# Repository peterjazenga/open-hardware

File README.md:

# open-hardware

This card combines positions for STM32 Bluepill, Arduino Nano and ESP32 Devkit 1 with a breakout area for both SMD and PTH IC's
The power bus is 3v3 from the compute board
It's a quick design for easing rapid prototyping and nothing more
There is no warranty whatsoever with this design, the user assumes all risks and liabilities
Under no circumstances will the author be held liable for use of this design or inability to use this design
No warranty is provided
WARNING: there is no verification of correct layout or function, the user must do their own verification

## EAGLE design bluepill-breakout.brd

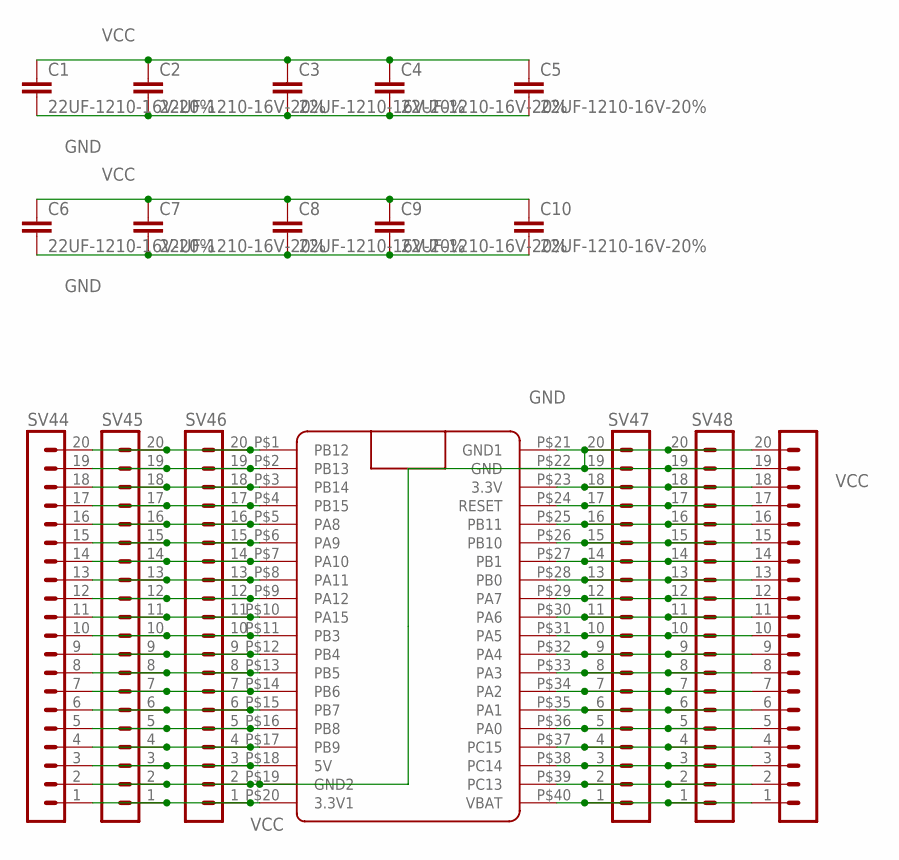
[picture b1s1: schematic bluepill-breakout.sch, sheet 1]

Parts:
C1, C2, C3, C4, C5, C6, C7, C8, C9, C10: 22UF-1210-16V-20%; 1210
SV44, SV45, SV46, SV47, SV48, SV50: MA20-1
U$1: BLUE_PILLADVANCED; BLUE_PILL_ADV

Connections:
GND: C1.2, C2.2, C3.2, C4.2, C5.2, C6.2, C7.2, C8.2, C9.2, C10.2, SV44.2, SV45.2, SV46.2, SV47.19, SV47.20, SV48.19, SV48.20, SV50.19, SV50.20, U$1.P$19 (GND2), U$1.P$21 (GND1), U$1.P$22 (GND); also elsewhere on the board
unnamed: SV44.3, SV45.3, SV46.3, U$1.P$18 (5V)
unnamed: SV44.4, SV45.4, SV46.4, U$1.P$17 (PB9)
unnamed: SV44.5, SV45.5, SV46.5, U$1.P$16 (PB8)
unnamed: SV44.6, SV45.6, SV46.6, U$1.P$15 (PB7)
unnamed: SV44.7, SV45.7, SV46.7, U$1.P$14 (PB6)
unnamed: SV44.8, SV45.8, SV46.8, U$1.P$13 (PB5)
unnamed: SV44.9, SV45.9, SV46.9, U$1.P$12 (PB4)
unnamed: SV44.10, SV45.10, SV46.10, U$1.P$11 (PB3)
unnamed: SV44.11, SV45.11, SV46.11, U$1.P$10 (PA15)
unnamed: SV44.12, SV45.12, SV46.12, U$1.P$9 (PA12)
unnamed: SV44.13, SV45.13, SV46.13, U$1.P$8 (PA11)
unnamed: SV44.14, SV45.14, SV46.14, U$1.P$7 (PA10)
unnamed: SV44.15, SV45.15, SV46.15, U$1.P$6 (PA9)
unnamed: SV44.16, SV45.16, SV46.16, U$1.P$5 (PA8)
unnamed: SV44.17, SV45.17, SV46.17, U$1.P$4 (PB15)
unnamed: SV44.18, SV45.18, SV46.18, U$1.P$3 (PB14)
unnamed: SV44.19, SV45.19, SV46.19, U$1.P$2 (PB13)
unnamed: SV44.20, SV45.20, SV46.20, U$1.P$1 (PB12)
unnamed: SV47.1, SV48.1, SV50.1, U$1.P$40 (VBAT)
unnamed: SV47.2, SV48.2, SV50.2, U$1.P$39 (PC13)
unnamed: SV47.3, SV48.3, SV50.3, U$1.P$38 (PC14)
unnamed: SV47.4, SV48.4, SV50.4, U$1.P$37 (PC15)
unnamed: SV47.5, SV48.5, SV50.5, U$1.P$36 (PA0)
unnamed: SV47.6, SV48.6, SV50.6, U$1.P$35 (PA1)
unnamed: SV47.7, SV48.7, SV50.7, U$1.P$34 (PA2)
unnamed: SV47.8, SV48.8, SV50.8, U$1.P$33 (PA3)
unnamed: SV47.9, SV48.9, SV50.9, U$1.P$32 (PA4)
unnamed: SV47.10, SV48.10, SV50.10, U$1.P$31 (PA5)
unnamed: SV47.11, SV48.11, SV50.11, U$1.P$30 (PA6)
unnamed: SV47.12, SV48.12, SV50.12, U$1.P$29 (PA7)
unnamed: SV47.13, SV48.13, SV50.13, U$1.P$28 (PB0)
unnamed: SV47.14, SV48.14, SV50.14, U$1.P$27 (PB1)
unnamed: SV47.15, SV48.15, SV50.15, U$1.P$26 (PB10)
unnamed: SV47.16, SV48.16, SV50.16, U$1.P$25 (PB11)
unnamed: SV47.17, SV48.17, SV50.17, U$1.P$24 (RESET)
VCC: C1.1, C2.1, C3.1, C4.1, C5.1, C6.1, C7.1, C8.1, C9.1, C10.1, SV44.1, SV45.1, SV46.1, SV47.18, SV48.18, SV50.18, U$1.P$20 (3.3V1), U$1.P$23 (3.3V); also elsewhere on the board

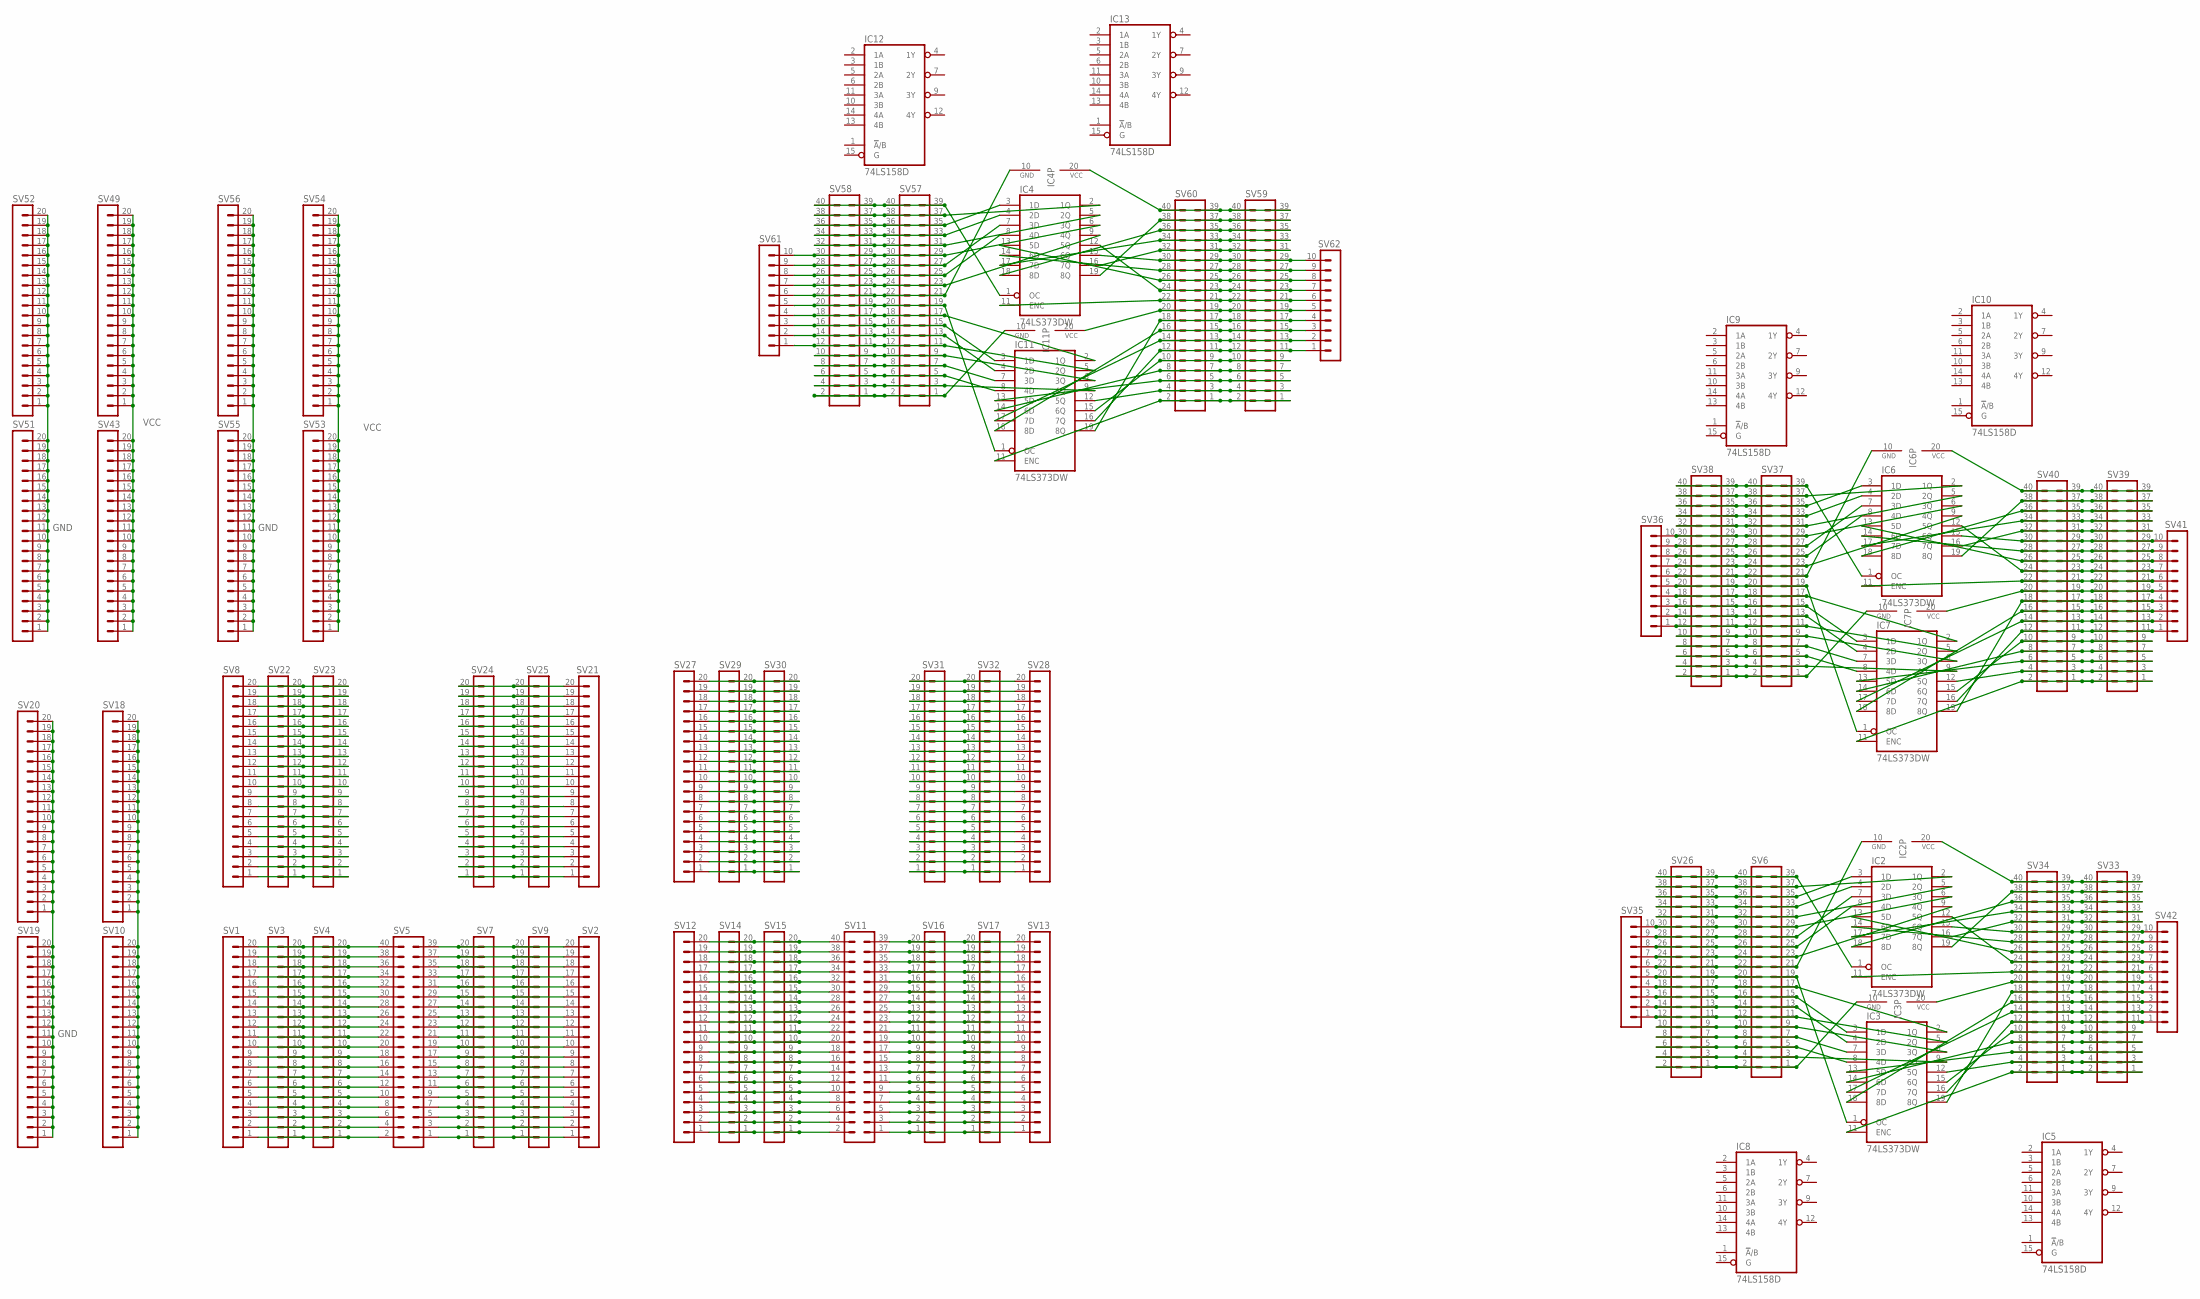
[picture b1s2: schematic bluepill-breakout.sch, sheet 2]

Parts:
IC2, IC3, IC4, IC6, IC7, IC11: 74LS373DW; SO20W
IC5, IC8, IC9, IC10, IC12, IC13: 74LS158D; SO16
SV1, SV2, SV3, SV4, SV7, SV8, SV9, SV10, SV12, SV13, SV14, SV15, SV16, SV17, SV18, SV19, SV20, SV21, SV22, SV23, SV24, SV25, SV27, SV28, SV29, SV30, SV31, SV32, SV43, SV49, SV51, SV52, SV53, SV54, SV55, SV56: MA20-1
SV5, SV6, SV11, SV26, SV33, SV34, SV37, SV38, SV39, SV40, SV57, SV58, SV59, SV60: MA20-2
SV35, SV36, SV41, SV42, SV61, SV62: MA10-1

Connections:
GND: IC5.8 (GND), IC8.8 (GND), IC9.8 (GND), IC10.8 (GND), IC12.8 (GND), IC13.8 (GND), SV19.1, SV19.2, SV19.3, SV19.4, SV19.5, SV19.6, SV19.7, SV19.8, SV19.9, SV19.10, SV19.11, SV19.12, SV19.13, SV19.14, SV19.15, SV19.16, SV19.17, SV19.18, SV19.19, SV19.20, SV20.1, SV20.2, SV20.3, SV20.4, SV20.5, SV20.6, SV20.7, SV20.8, SV20.9, SV20.10, SV20.11, SV20.12, SV20.13, SV20.14, SV20.15, SV20.16, SV20.17, SV20.18, SV20.19, SV20.20, SV51.1, SV51.2, SV51.3, SV51.4, SV51.5, SV51.6, SV51.7, SV51.8, SV51.9, SV51.10, SV51.11, SV51.12, SV51.13, SV51.14, SV51.15, SV51.16, SV51.17, SV51.18, SV51.19, SV51.20, SV52.1, SV52.2, SV52.3, SV52.4, SV52.5, SV52.6, SV52.7, SV52.8, SV52.9, SV52.10, SV52.11, SV52.12, SV52.13, SV52.14, SV52.15, SV52.16, SV52.17, SV52.18, SV52.19, SV52.20, SV55.1, SV55.2, SV55.3, SV55.4, SV55.5, SV55.6, SV55.7, SV55.8, SV55.9, SV55.10, SV55.11, SV55.12, SV55.13, SV55.14, SV55.15, SV55.16, SV55.17, SV55.18, SV55.19, SV55.20, SV56.1, SV56.2, SV56.3, SV56.4, SV56.5, SV56.6, SV56.7, SV56.8, SV56.9, SV56.10, SV56.11, SV56.12, SV56.13, SV56.14, SV56.15, SV56.16, SV56.17, SV56.18, SV56.19, SV56.20; also elsewhere on the board
unnamed: SV1.1, SV3.1, SV4.1, SV5.2
unnamed: SV1.2, SV3.2, SV4.2, SV5.4
unnamed: SV1.3, SV3.3, SV4.3, SV5.6
unnamed: SV1.4, SV3.4, SV4.4, SV5.8
unnamed: SV1.5, SV3.5, SV4.5, SV5.10
unnamed: SV1.6, SV3.6, SV4.6, SV5.12
unnamed: SV1.7, SV3.7, SV4.7, SV5.14
unnamed: SV1.8, SV3.8, SV4.8, SV5.16
unnamed: SV1.9, SV3.9, SV4.9, SV5.18
unnamed: SV1.10, SV3.10, SV4.10, SV5.20
unnamed: SV1.11, SV3.11, SV4.11, SV5.22
unnamed: SV1.12, SV3.12, SV4.12, SV5.24
unnamed: SV1.13, SV3.13, SV4.13, SV5.26
unnamed: SV1.14, SV3.14, SV4.14, SV5.28
unnamed: SV1.15, SV3.15, SV4.15, SV5.30
unnamed: SV1.16, SV3.16, SV4.16, SV5.32
unnamed: SV1.17, SV3.17, SV4.17, SV5.34
unnamed: SV1.18, SV3.18, SV4.18, SV5.36
unnamed: SV1.19, SV3.19, SV4.19, SV5.38
unnamed: SV1.20, SV3.20, SV4.20, SV5.40
unnamed: SV2.1, SV5.1, SV7.1, SV9.1
unnamed: SV2.2, SV5.3, SV7.2, SV9.2
unnamed: SV2.3, SV5.5, SV7.3, SV9.3
unnamed: SV2.4, SV5.7, SV7.4, SV9.4
unnamed: SV2.5, SV5.9, SV7.5, SV9.5
unnamed: SV2.6, SV5.11, SV7.6, SV9.6
unnamed: SV2.7, SV5.13, SV7.7, SV9.7
unnamed: SV2.8, SV5.15, SV7.8, SV9.8
unnamed: SV2.9, SV5.17, SV7.9, SV9.9
unnamed: SV2.10, SV5.19, SV7.10, SV9.10
unnamed: SV2.11, SV5.21, SV7.11, SV9.11
unnamed: SV2.12, SV5.23, SV7.12, SV9.12
unnamed: SV2.13, SV5.25, SV7.13, SV9.13
unnamed: SV2.14, SV5.27, SV7.14, SV9.14
unnamed: SV2.15, SV5.29, SV7.15, SV9.15
unnamed: SV2.16, SV5.31, SV7.16, SV9.16
unnamed: SV2.17, SV5.33, SV7.17, SV9.17
unnamed: SV2.18, SV5.35, SV7.18, SV9.18
unnamed: SV2.19, SV5.37, SV7.19, SV9.19
unnamed: SV2.20, SV5.39, SV7.20, SV9.20
unnamed: SV11.2, SV12.1, SV14.1, SV15.1
unnamed: SV11.4, SV12.2, SV14.2, SV15.2
unnamed: SV11.6, SV12.3, SV14.3, SV15.3
unnamed: SV11.8, SV12.4, SV14.4, SV15.4
unnamed: SV11.10, SV12.5, SV14.5, SV15.5
unnamed: SV11.12, SV12.6, SV14.6, SV15.6
unnamed: SV11.14, SV12.7, SV14.7, SV15.7
unnamed: SV11.16, SV12.8, SV14.8, SV15.8
unnamed: SV11.18, SV12.9, SV14.9, SV15.9
unnamed: SV11.20, SV12.10, SV14.10, SV15.10
unnamed: SV11.22, SV12.11, SV14.11, SV15.11
unnamed: SV11.24, SV12.12, SV14.12, SV15.12
unnamed: SV11.26, SV12.13, SV14.13, SV15.13
unnamed: SV11.28, SV12.14, SV14.14, SV15.14
unnamed: SV11.30, SV12.15, SV14.15, SV15.15
unnamed: SV11.32, SV12.16, SV14.16, SV15.16
unnamed: SV11.34, SV12.17, SV14.17, SV15.17
unnamed: SV11.36, SV12.18, SV14.18, SV15.18
unnamed: SV11.38, SV12.19, SV14.19, SV15.19
unnamed: SV11.40, SV12.20, SV14.20, SV15.20
unnamed: SV11.1, SV13.1, SV16.1, SV17.1
unnamed: SV11.3, SV13.2, SV16.2, SV17.2
unnamed: SV11.5, SV13.3, SV16.3, SV17.3
unnamed: SV11.7, SV13.4, SV16.4, SV17.4
unnamed: SV11.9, SV13.5, SV16.5, SV17.5
unnamed: SV11.11, SV13.6, SV16.6, SV17.6
unnamed: SV11.13, SV13.7, SV16.7, SV17.7
unnamed: SV11.15, SV13.8, SV16.8, SV17.8
unnamed: SV11.17, SV13.9, SV16.9, SV17.9
unnamed: SV11.19, SV13.10, SV16.10, SV17.10
unnamed: SV11.21, SV13.11, SV16.11, SV17.11
unnamed: SV11.23, SV13.12, SV16.12, SV17.12
unnamed: SV11.25, SV13.13, SV16.13, SV17.13
unnamed: SV11.27, SV13.14, SV16.14, SV17.14
unnamed: SV11.29, SV13.15, SV16.15, SV17.15
unnamed: SV11.31, SV13.16, SV16.16, SV17.16
unnamed: SV11.33, SV13.17, SV16.17, SV17.17
unnamed: SV11.35, SV13.18, SV16.18, SV17.18
unnamed: SV11.37, SV13.19, SV16.19, SV17.19
unnamed: SV11.39, SV13.20, SV16.20, SV17.20
unnamed: SV8.1, SV22.1, SV23.1
unnamed: SV8.2, SV22.2, SV23.2
unnamed: SV8.3, SV22.3, SV23.3
unnamed: SV8.4, SV22.4, SV23.4
unnamed: SV8.5, SV22.5, SV23.5
unnamed: SV8.6, SV22.6, SV23.6
unnamed: SV8.7, SV22.7, SV23.7
unnamed: SV8.8, SV22.8, SV23.8
unnamed: SV8.9, SV22.9, SV23.9
unnamed: SV8.10, SV22.10, SV23.10
unnamed: SV8.11, SV22.11, SV23.11
unnamed: SV8.12, SV22.12, SV23.12
unnamed: SV8.13, SV22.13, SV23.13
unnamed: SV8.14, SV22.14, SV23.14
unnamed: SV8.15, SV22.15, SV23.15
unnamed: SV8.16, SV22.16, SV23.16
unnamed: SV8.17, SV22.17, SV23.17
unnamed: SV8.18, SV22.18, SV23.18
unnamed: SV8.19, SV22.19, SV23.19
unnamed: SV8.20, SV22.20, SV23.20
unnamed: SV21.1, SV24.1, SV25.1
unnamed: SV21.2, SV24.2, SV25.2
unnamed: SV21.3, SV24.3, SV25.3
unnamed: SV21.4, SV24.4, SV25.4
unnamed: SV21.5, SV24.5, SV25.5
unnamed: SV21.6, SV24.6, SV25.6
unnamed: SV21.7, SV24.7, SV25.7
unnamed: SV21.8, SV24.8, SV25.8
unnamed: SV21.9, SV24.9, SV25.9
unnamed: SV21.10, SV24.10, SV25.10
unnamed: SV21.11, SV24.11, SV25.11
unnamed: SV21.12, SV24.12, SV25.12
unnamed: SV21.13, SV24.13, SV25.13
unnamed: SV21.14, SV24.14, SV25.14
unnamed: SV21.15, SV24.15, SV25.15
unnamed: SV21.16, SV24.16, SV25.16
unnamed: SV21.17, SV24.17, SV25.17
unnamed: SV21.18, SV24.18, SV25.18
unnamed: SV21.19, SV24.19, SV25.19
unnamed: SV21.20, SV24.20, SV25.20
unnamed: SV27.1, SV29.1, SV30.1
unnamed: SV27.2, SV29.2, SV30.2
unnamed: SV27.3, SV29.3, SV30.3
unnamed: SV27.4, SV29.4, SV30.4
unnamed: SV27.5, SV29.5, SV30.5
unnamed: SV27.6, SV29.6, SV30.6
unnamed: SV27.7, SV29.7, SV30.7
unnamed: SV27.8, SV29.8, SV30.8
unnamed: SV27.9, SV29.9, SV30.9
unnamed: SV27.10, SV29.10, SV30.10
unnamed: SV27.11, SV29.11, SV30.11
unnamed: SV27.12, SV29.12, SV30.12
unnamed: SV27.13, SV29.13, SV30.13
unnamed: SV27.14, SV29.14, SV30.14
unnamed: SV27.15, SV29.15, SV30.15
unnamed: SV27.16, SV29.16, SV30.16
unnamed: SV27.17, SV29.17, SV30.17
unnamed: SV27.18, SV29.18, SV30.18
unnamed: SV27.19, SV29.19, SV30.19
unnamed: SV27.20, SV29.20, SV30.20
unnamed: SV28.1, SV31.1, SV32.1
unnamed: SV28.2, SV31.2, SV32.2
unnamed: SV28.3, SV31.3, SV32.3
unnamed: SV28.4, SV31.4, SV32.4
unnamed: SV28.5, SV31.5, SV32.5
unnamed: SV28.6, SV31.6, SV32.6
unnamed: SV28.7, SV31.7, SV32.7
unnamed: SV28.8, SV31.8, SV32.8
unnamed: SV28.9, SV31.9, SV32.9
unnamed: SV28.10, SV31.10, SV32.10
unnamed: SV28.11, SV31.11, SV32.11
unnamed: SV28.12, SV31.12, SV32.12
unnamed: SV28.13, SV31.13, SV32.13
unnamed: SV28.14, SV31.14, SV32.14
unnamed: SV28.15, SV31.15, SV32.15
unnamed: SV28.16, SV31.16, SV32.16
unnamed: SV28.17, SV31.17, SV32.17
unnamed: SV28.18, SV31.18, SV32.18
unnamed: SV28.19, SV31.19, SV32.19
unnamed: SV28.20, SV31.20, SV32.20
unnamed: IC3.10 (GND), SV6.1, SV6.2, SV26.1, SV26.2
unnamed: IC3.9 (4Q), SV6.3, SV6.4, SV26.3, SV26.4
unnamed: IC3.8 (4D), SV6.5, SV6.6, SV26.5, SV26.6
unnamed: IC3.7 (3D), SV6.7, SV6.8, SV26.7, SV26.8
unnamed: IC3.6 (3Q), SV6.9, SV6.10, SV26.9, SV26.10
unnamed: IC3.5 (2Q), SV6.11, SV6.12, SV26.11, SV26.12, SV35.1
unnamed: IC3.4 (2D), SV6.13, SV6.14, SV26.13, SV26.14, SV35.2
unnamed: IC3.3 (1D), SV6.15, SV6.16, SV26.15, SV26.16, SV35.3
unnamed: IC3.2 (1Q), SV6.17, SV6.18, SV26.17, SV26.18, SV35.4
unnamed: IC3.1 (OC), SV6.19, SV6.20, SV26.19, SV26.20, SV35.5
unnamed: IC2.10 (GND), SV6.21, SV6.22, SV26.21, SV26.22, SV35.6
unnamed: IC2.9 (4Q), SV6.23, SV6.24, SV26.23, SV26.24, SV35.7
unnamed: IC2.8 (4D), SV6.25, SV6.26, SV26.25, SV26.26, SV35.8
unnamed: IC2.7 (3D), SV6.27, SV6.28, SV26.27, SV26.28, SV35.9
unnamed: IC2.6 (3Q), SV6.29, SV6.30, SV26.29, SV26.30, SV35.10
unnamed: IC2.5 (2Q), SV6.31, SV6.32, SV26.31, SV26.32
unnamed: IC2.4 (2D), SV6.33, SV6.34, SV26.33, SV26.34
unnamed: IC2.3 (1D), SV6.35, SV6.36, SV26.35, SV26.36
unnamed: IC2.2 (1Q), SV6.37, SV6.38, SV26.37, SV26.38
unnamed: IC2.1 (OC), SV6.39, SV6.40, SV26.39, SV26.40
unnamed: IC3.11 (ENC), SV33.1, SV33.2, SV34.1, SV34.2
unnamed: IC3.12 (5Q), SV33.3, SV33.4, SV34.3, SV34.4
unnamed: IC3.13 (5D), SV33.5, SV33.6, SV34.5, SV34.6
unnamed: IC3.14 (6D), SV33.7, SV33.8, SV34.7, SV34.8
unnamed: IC3.15 (6Q), SV33.9, SV33.10, SV34.9, SV34.10
unnamed: IC3.16 (7Q), SV33.11, SV33.12, SV34.11, SV34.12, SV42.1
unnamed: IC3.17 (7D), SV33.13, SV33.14, SV34.13, SV34.14, SV42.2
unnamed: IC3.18 (8D), SV33.15, SV33.16, SV34.15, SV34.16, SV42.3
unnamed: IC3.19 (8Q), SV33.17, SV33.18, SV34.17, SV34.18, SV42.4
unnamed: IC3.20 (VCC), SV33.19, SV33.20, SV34.19, SV34.20, SV42.5
unnamed: IC2.11 (ENC), SV33.21, SV33.22, SV34.21, SV34.22, SV42.6
unnamed: IC2.12 (5Q), SV33.23, SV33.24, SV34.23, SV34.24, SV42.7
unnamed: IC2.13 (5D), SV33.25, SV33.26, SV34.25, SV34.26, SV42.8
unnamed: IC2.14 (6D), SV33.27, SV33.28, SV34.27, SV34.28, SV42.9
unnamed: IC2.15 (6Q), SV33.29, SV33.30, SV34.29, SV34.30, SV42.10
unnamed: IC2.16 (7Q), SV33.31, SV33.32, SV34.31, SV34.32
unnamed: IC2.17 (7D), SV33.33, SV33.34, SV34.33, SV34.34
unnamed: IC2.18 (8D), SV33.35, SV33.36, SV34.35, SV34.36
unnamed: IC2.19 (8Q), SV33.37, SV33.38, SV34.37, SV34.38
unnamed: IC2.20 (VCC), SV33.39, SV33.40, SV34.39, SV34.40
unnamed: IC11.9 (4Q), SV57.3, SV57.4, SV58.3, SV58.4
unnamed: IC11.7 (3D), SV57.7, SV57.8, SV58.7, SV58.8
unnamed: IC11.6 (3Q), SV57.9, SV57.10, SV58.9, SV58.10
unnamed: IC11.5 (2Q), SV57.11, SV57.12, SV58.11, SV58.12, SV61.1
unnamed: IC11.3 (1D), SV57.15, SV57.16, SV58.15, SV58.16, SV61.3
unnamed: IC11.2 (1Q), SV57.17, SV57.18, SV58.17, SV58.18, SV61.4
unnamed: IC11.1 (OC), SV57.19, SV57.20, SV58.19, SV58.20, SV61.5
unnamed: IC4.10 (GND), SV57.21, SV57.22, SV58.21, SV58.22, SV61.6
unnamed: IC4.9 (4Q), SV57.23, SV57.24, SV58.23, SV58.24, SV61.7
unnamed: IC4.7 (3D), SV57.27, SV57.28, SV58.27, SV58.28, SV61.9
unnamed: IC4.6 (3Q), SV57.29, SV57.30, SV58.29, SV58.30, SV61.10
unnamed: IC4.5 (2Q), SV57.31, SV57.32, SV58.31, SV58.32
unnamed: IC4.3 (1D), SV57.35, SV57.36, SV58.35, SV58.36
unnamed: IC4.2 (1Q), SV57.37, SV57.38, SV58.37, SV58.38
unnamed: IC4.1 (OC), SV57.39, SV57.40, SV58.39, SV58.40
unnamed: IC11.11 (ENC), SV59.1, SV59.2, SV60.1, SV60.2
unnamed: IC11.12 (5Q), SV59.3, SV59.4, SV60.3, SV60.4
unnamed: IC11.13 (5D), SV59.5, SV59.6, SV60.5, SV60.6
unnamed: IC11.14 (6D), SV59.7, SV59.8, SV60.7, SV60.8
unnamed: IC11.15 (6Q), SV59.9, SV59.10, SV60.9, SV60.10
unnamed: IC11.16 (7Q), SV59.11, SV59.12, SV60.11, SV60.12, SV62.1
unnamed: IC11.17 (7D), SV59.13, SV59.14, SV60.13, SV60.14, SV62.2
unnamed: IC11.18 (8D), SV59.15, SV59.16, SV60.15, SV60.16, SV62.3
unnamed: IC11.19 (8Q), SV59.17, SV59.18, SV60.17, SV60.18, SV62.4
unnamed: IC11.20 (VCC), SV59.19, SV59.20, SV60.19, SV60.20, SV62.5
unnamed: IC4.11 (ENC), SV59.21, SV59.22, SV60.21, SV60.22, SV62.6
unnamed: IC4.12 (5Q), SV59.23, SV59.24, SV60.23, SV60.24, SV62.7
unnamed: IC4.13 (5D), SV59.25, SV59.26, SV60.25, SV60.26, SV62.8
unnamed: IC4.14 (6D), SV59.27, SV59.28, SV60.27, SV60.28, SV62.9
unnamed: IC4.15 (6Q), SV59.29, SV59.30, SV60.29, SV60.30, SV62.10
unnamed: IC4.16 (7Q), SV59.31, SV59.32, SV60.31, SV60.32
unnamed: IC4.17 (7D), SV59.33, SV59.34, SV60.33, SV60.34
unnamed: IC4.18 (8D), SV59.35, SV59.36, SV60.35, SV60.36
unnamed: IC4.19 (8Q), SV59.37, SV59.38, SV60.37, SV60.38
unnamed: IC11.10 (GND), SV57.1, SV57.2, SV58.1, SV58.2
unnamed: IC11.8 (4D), SV57.5, SV57.6, SV58.5, SV58.6
unnamed: IC11.4 (2D), SV57.13, SV57.14, SV58.13, SV58.14, SV61.2
unnamed: IC4.8 (4D), SV57.25, SV57.26, SV58.25, SV58.26, SV61.8
unnamed: IC4.4 (2D), SV57.33, SV57.34, SV58.33, SV58.34
unnamed: IC4.20 (VCC), SV59.39, SV59.40, SV60.39, SV60.40
unnamed: IC7.10 (GND), SV37.1, SV37.2, SV38.1, SV38.2
unnamed: IC7.9 (4Q), SV37.3, SV37.4, SV38.3, SV38.4
unnamed: IC7.8 (4D), SV37.5, SV37.6, SV38.5, SV38.6
unnamed: IC7.7 (3D), SV37.7, SV37.8, SV38.7, SV38.8
unnamed: IC7.6 (3Q), SV37.9, SV37.10, SV38.9, SV38.10
unnamed: IC7.5 (2Q), SV36.1, SV37.11, SV37.12, SV38.11, SV38.12
unnamed: IC7.4 (2D), SV36.2, SV37.13, SV37.14, SV38.13, SV38.14
unnamed: IC7.3 (1D), SV36.3, SV37.15, SV37.16, SV38.15, SV38.16
unnamed: IC7.2 (1Q), SV36.4, SV37.17, SV37.18, SV38.17, SV38.18
unnamed: IC7.1 (OC), SV36.5, SV37.19, SV37.20, SV38.19, SV38.20
unnamed: IC6.10 (GND), SV36.6, SV37.21, SV37.22, SV38.21, SV38.22
unnamed: IC6.9 (4Q), SV36.7, SV37.23, SV37.24, SV38.23, SV38.24
unnamed: IC6.8 (4D), SV36.8, SV37.25, SV37.26, SV38.25, SV38.26
unnamed: IC6.7 (3D), SV36.9, SV37.27, SV37.28, SV38.27, SV38.28
unnamed: IC6.6 (3Q), SV36.10, SV37.29, SV37.30, SV38.29, SV38.30
unnamed: IC6.5 (2Q), SV37.31, SV37.32, SV38.31, SV38.32
unnamed: IC6.4 (2D), SV37.33, SV37.34, SV38.33, SV38.34
unnamed: IC6.3 (1D), SV37.35, SV37.36, SV38.35, SV38.36
unnamed: IC6.2 (1Q), SV37.37, SV37.38, SV38.37, SV38.38
unnamed: IC6.1 (OC), SV37.39, SV37.40, SV38.39, SV38.40
unnamed: IC7.11 (ENC), SV39.1, SV39.2, SV40.1, SV40.2
unnamed: IC7.12 (5Q), SV39.3, SV39.4, SV40.3, SV40.4
unnamed: IC7.13 (5D), SV39.5, SV39.6, SV40.5, SV40.6
unnamed: IC7.14 (6D), SV39.7, SV39.8, SV40.7, SV40.8
unnamed: IC7.15 (6Q), SV39.9, SV39.10, SV40.9, SV40.10
unnamed: IC7.16 (7Q), SV39.11, SV39.12, SV40.11, SV40.12, SV41.1
unnamed: IC7.17 (7D), SV39.13, SV39.14, SV40.13, SV40.14, SV41.2
unnamed: IC7.18 (8D), SV39.15, SV39.16, SV40.15, SV40.16, SV41.3
unnamed: IC7.19 (8Q), SV39.17, SV39.18, SV40.17, SV40.18, SV41.4
unnamed: IC7.20 (VCC), SV39.19, SV39.20, SV40.19, SV40.20, SV41.5
unnamed: IC6.11 (ENC), SV39.21, SV39.22, SV40.21, SV40.22, SV41.6
unnamed: IC6.12 (5Q), SV39.23, SV39.24, SV40.23, SV40.24, SV41.7
unnamed: IC6.13 (5D), SV39.25, SV39.26, SV40.25, SV40.26, SV41.8
unnamed: IC6.14 (6D), SV39.27, SV39.28, SV40.27, SV40.28, SV41.9
unnamed: IC6.15 (6Q), SV39.29, SV39.30, SV40.29, SV40.30, SV41.10
unnamed: IC6.16 (7Q), SV39.31, SV39.32, SV40.31, SV40.32
unnamed: IC6.17 (7D), SV39.33, SV39.34, SV40.33, SV40.34
unnamed: IC6.18 (8D), SV39.35, SV39.36, SV40.35, SV40.36
unnamed: IC6.19 (8Q), SV39.37, SV39.38, SV40.37, SV40.38
unnamed: IC6.20 (VCC), SV39.39, SV39.40, SV40.39, SV40.40
VCC: IC5.16 (VCC), IC8.16 (VCC), IC9.16 (VCC), IC10.16 (VCC), IC12.16 (VCC), IC13.16 (VCC), SV10.1, SV10.2, SV10.3, SV10.4, SV10.5, SV10.6, SV10.7, SV10.8, SV10.9, SV10.10, SV10.11, SV10.12, SV10.13, SV10.14, SV10.15, SV10.16, SV10.17, SV10.18, SV10.19, SV10.20, SV18.1, SV18.2, SV18.3, SV18.4, SV18.5, SV18.6, SV18.7, SV18.8, SV18.9, SV18.10, SV18.11, SV18.12, SV18.13, SV18.14, SV18.15, SV18.16, SV18.17, SV18.18, SV18.19, SV18.20, SV43.1, SV43.2, SV43.3, SV43.4, SV43.5, SV43.6, SV43.7, SV43.8, SV43.9, SV43.10, SV43.11, SV43.12, SV43.13, SV43.14, SV43.15, SV43.16, SV43.17, SV43.18, SV43.19, SV43.20, SV49.1, SV49.2, SV49.3, SV49.4, SV49.5, SV49.6, SV49.7, SV49.8, SV49.9, SV49.10, SV49.11, SV49.12, SV49.13, SV49.14, SV49.15, SV49.16, SV49.17, SV49.18, SV49.19, SV49.20, SV53.1, SV53.2, SV53.3, SV53.4, SV53.5, SV53.6, SV53.7, SV53.8, SV53.9, SV53.10, SV53.11, SV53.12, SV53.13, SV53.14, SV53.15, SV53.16, SV53.17, SV53.18, SV53.19, SV53.20, SV54.1, SV54.2, SV54.3, SV54.4, SV54.5, SV54.6, SV54.7, SV54.8, SV54.9, SV54.10, SV54.11, SV54.12, SV54.13, SV54.14, SV54.15, SV54.16, SV54.17, SV54.18, SV54.19, SV54.20; also elsewhere on the board

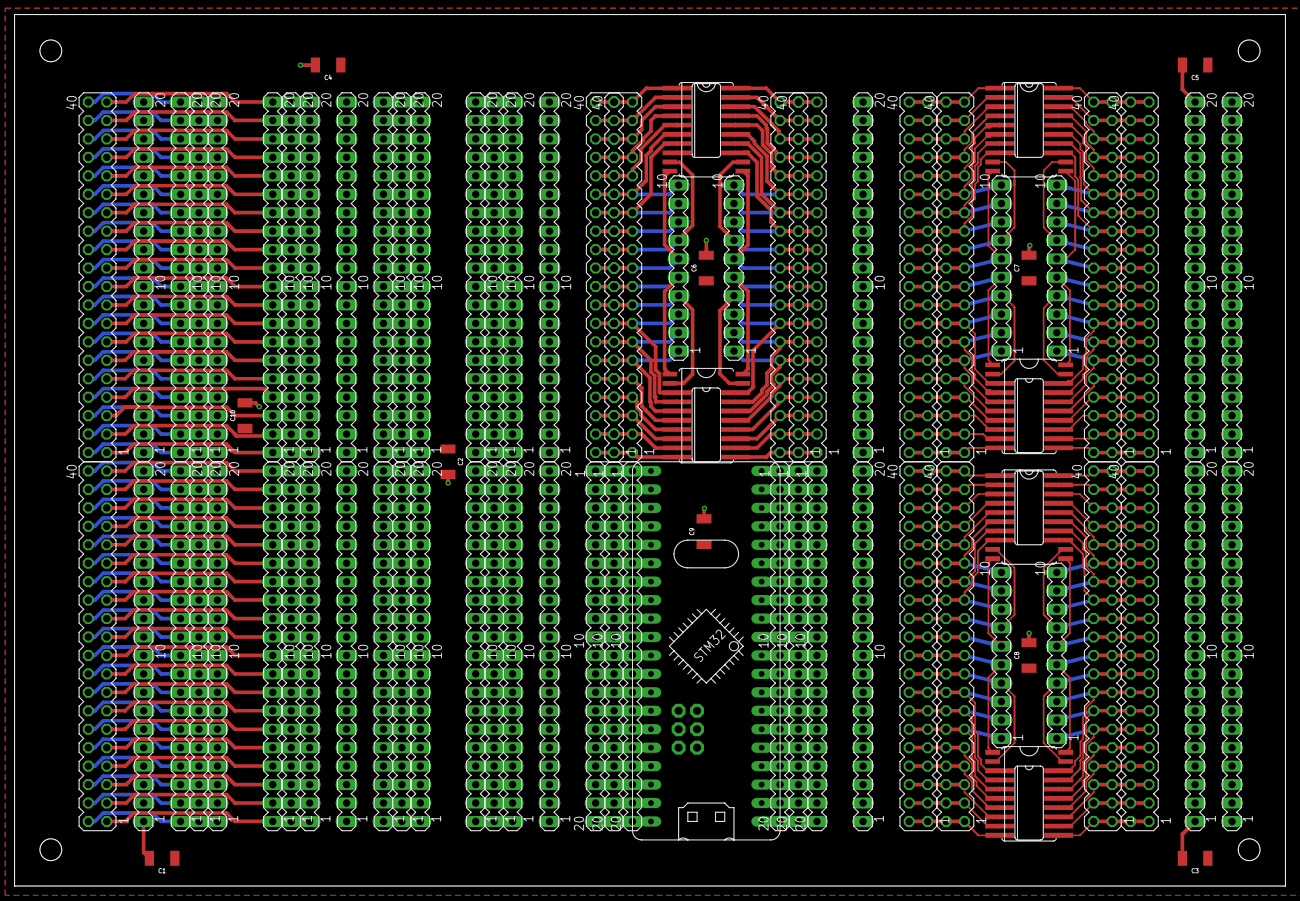
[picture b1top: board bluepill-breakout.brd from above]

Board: 2 copper layers, 175.0 x 120.0 mm, 85 parts (0 on the bottom side), 317 nets.

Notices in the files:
nano-esp-stm-breakout.brd:
Copyright ©2021, Released under the Creative Commons License
parts and their libraries:
SparkFun-Capacitors: Licensing: Creative Commons ShareAlike 4.0 International - https://creativecommons.org/licenses/by-sa/4.0
